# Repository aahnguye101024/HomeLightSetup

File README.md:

# HomeLightSetup
This project features 2 boards that work together to turn on strips of SK9822 wirelessly and either turn on them using my iphone with shortcuts through wifi or through the main board through a cap touch interface. The main board having an esp32 pico d4 with an antenna for WiFi access, a cap touch ic, and additions to support a lipo battery. The auxiliary board features an esp32 pico d4 with an antenna to communicate with the main board and a hefty 12V to 5V buck to run lights off of.

# Main Board

# Auxiliary Board

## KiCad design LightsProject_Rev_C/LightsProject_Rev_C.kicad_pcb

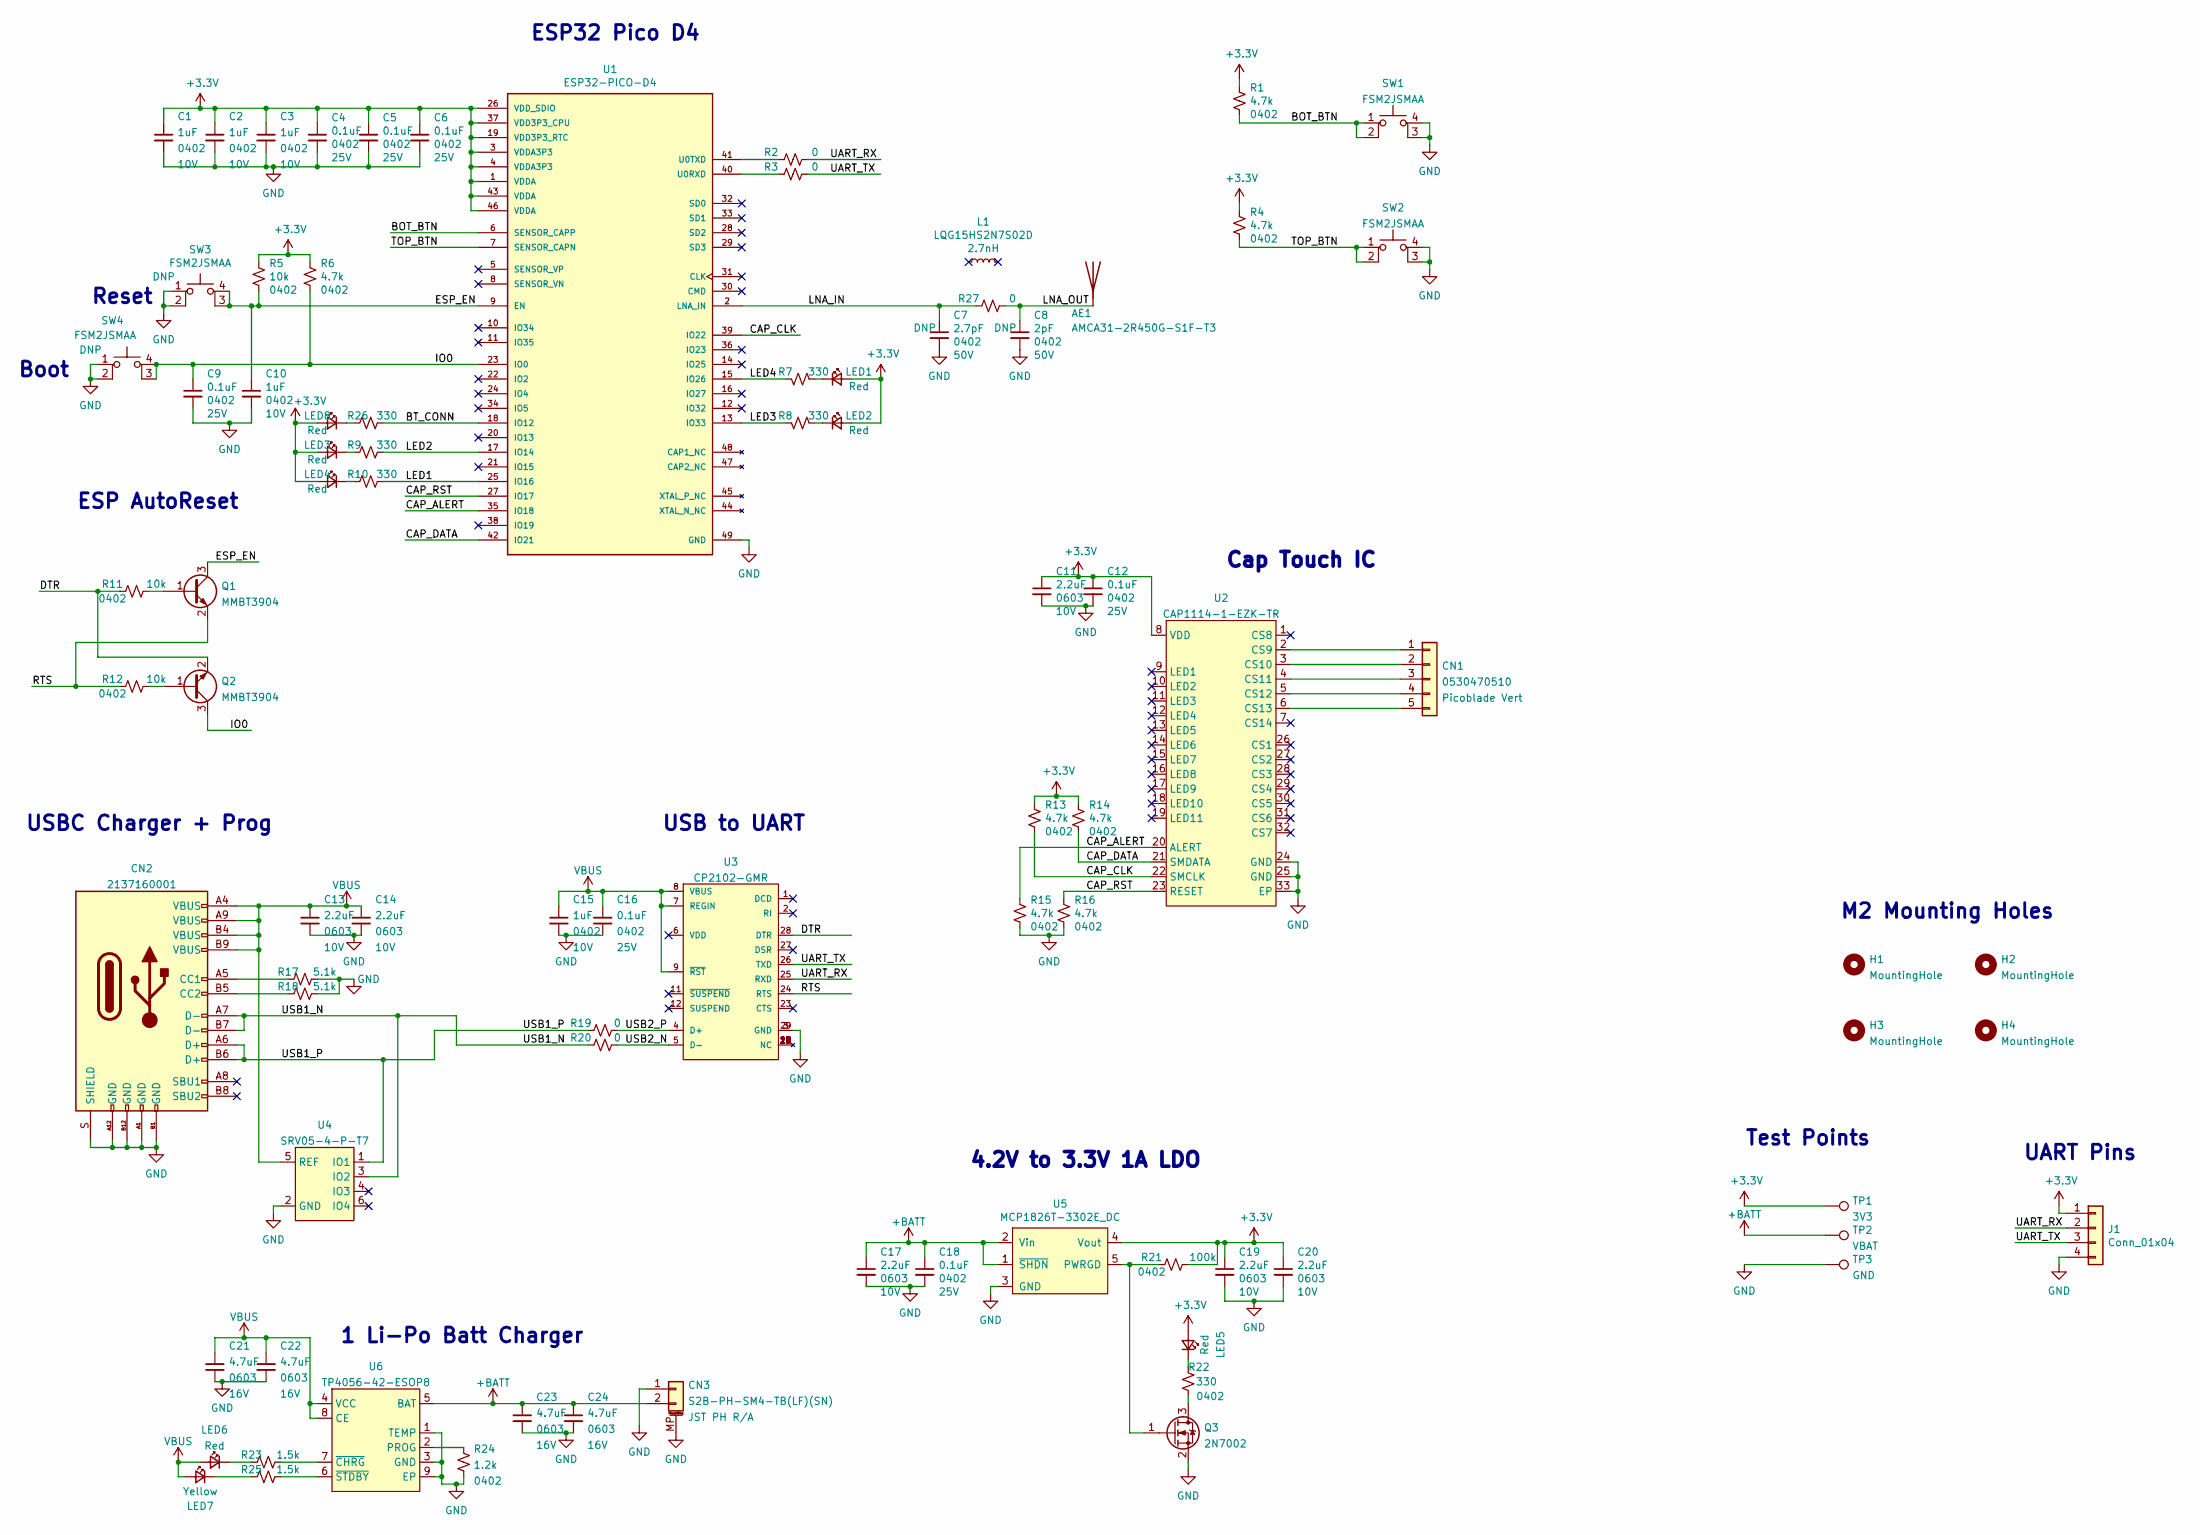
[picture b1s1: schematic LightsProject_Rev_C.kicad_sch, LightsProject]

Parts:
AE1: AMCA31-2R450G-S1F-T3; ANT_AMCA31-2R450G-S1F-T3; Part Number 535-14095-1-ND
C1, C2, C3, C10, C15: 1uF; C_0402_1005Metric; Voltage 10V; Part Number 1276-1076-1-ND
C4, C5, C6, C9, C12, C16, C18: 0.1uF; C_0402_1005Metric; Voltage 25V; Part Number 1276-1043-1-ND
C7: 2.7pF; C_0402_1005Metric; Voltage 50V; Part Number 311-1005-1-ND
C8: 2pF; C_0402_1005Metric; Voltage 50V; Part Number 311-1006-1-ND
C11, C13, C14, C17, C19, C20: 2.2uF; C_0603_1608Metric; Voltage 10V; Part Number 1276-1085-1-ND
C21, C22, C23, C24: 4.7uF; C_0603_1608Metric; Voltage 16V; Part Number 1276-1784-1-ND
CN1: 0530470510; Part Number WM1734-ND
CN2: 2137160001; Part Number 900-2137160001CT-ND
CN3: S2B-PH-SM4-TB(LF)(SN); JST_S2B-PH-SM4-TB(LF)(SN); Part Number 455-1749-1-ND
H1, H2, H3, H4: MountingHole; MountingHole_2.2mm_M2_ISO14580
J1: Conn_01x04; PinHeader_1x04_P2.54mm_Vertical
L1: LQG15HS2N7S02D; L_0402_1005Metric; Part Number 490-2615-1-ND
LED1, LED2, LED3, LED4, LED5, LED6, LED8: NCD0805R1; LED_0805_2012Metric; Part Number C84256
LED7: Y2C-CQ2R2L; LED_0603_1608Metric; Voltage 2.1V; Part Number C72038
Q1, Q2: MMBT3904; SOT-23; Part Number C20526
Q3: 2N7002; SOT-23; Part Number C8545; JLC Part Number C8545
R1, R4, R6, R13, R14, R15, R16: 4.7k; R_0402_1005Metric; Part Number RMCF0402FT4K70CT-ND
R2, R3, R19, R20, R27: 0; R_0402_1005Metric; Part Number RMCF0402ZT0R00CT-ND
R5, R11, R12: 10k; R_0402_1005Metric; Part Number RMCF0402FT10K0CT-ND
R7, R8, R9, R10, R22, R26: 330; R_0402_1005Metric; Part Number 311-330LRCT-ND
R17, R18: 5.1k; R_0402_1005Metric; Part Number 311-5.10KLRCT-ND
R21: 100k; R_0402_1005Metric; Part Number 2037-PFR05S-104-FNHCT-ND
R23, R25: 1.5k; R_0402_1005Metric; Part Number RMCF0402FT1K50CT-ND
R24: 1.2k; R_0402_1005Metric; Part Number YAG3447CT-ND
SW1, SW2, SW3, SW4: FSM2JSMAA; SW_2-1437565-8; Part Number 450-3355-ND
TP1: 3V3; CurrentTestPoint
TP2: VBAT; CurrentTestPoint
TP3: GND; CurrentTestPoint
U1: ESP32-PICO-D4; QFN-48-1EP_7x7mm_P0.5mm_EP5.3x5.3mm_ThermalVias; Part Number 1904-1029-1-ND
U2: CAP1114-1-EZK-TR; QFN-32-1EP_5x5mm_P0.5mm_EP3.1x3.1mm; Part Number Ologic
U3: CP2102-GMR; QFN28G_0.5-5X5MM; Part Number IC USB-TO-UART BRIDGE 28VQFN; JLC Part Number C6568
U4: SRV05-4-P-T7; SOT-23-6; Part Number C85364
U5: MCP1826T-3302E_DC; SOT-223-6_TabPin3; Part Number Ologic
U6: TP4056-42-ESOP8; HTSOP-8-1EP_3.9x4.9mm_P1.27mm_EP2.4x3.2mm; Part Number C16581

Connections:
+3V3: C1.1, C2.1, C3.1, C4.1, C5.1, C6.1, C11.1, C12.1, C19.1, C20.1, J1.1, LED1.2 (A), LED2.2 (A), LED3.2 (A), LED4.2 (A), LED5.2 (A), LED8.2 (A), R1.1, R4.1, R5.1, R6.1, R13.1, R14.1, R21.2, TP1.1, U1.1 (VDDA), U1.3 (VDDA3P3), U1.4 (VDDA3P3), U1.19 (VDD3P3_RTC), U1.26 (VDD_SDIO), U1.37 (VDD3P3_CPU), U1.43 (VDDA), U1.46 (VDDA), U2.8 (VDD), U5.4 (Vout)
+BATT: C17.1, C18.1, C23.1, C24.1, CN3.2, TP2.1, U5.1 (~SHDN), U5.2 (Vin), U6.5 (BAT)
/BOT_BTN: R1.2, SW1.1, SW1.2, U1.6 (SENSOR_CAPP)
/BT_CONN: R26.1, U1.18 (IO12)
/CAP_ALERT: R15.1, U1.35 (IO18), U2.20 (ALERT)
/CAP_CLK: R13.2, U1.39 (IO22), U2.22 (SMCLK)
/CAP_DATA: R14.2, U1.42 (IO21), U2.21 (SMDATA)
/CAP_RST: R16.1, U1.27 (IO17), U2.23 (RESET)
/DTR: Q2.2 (E), R11.2, U3.28 (DTR)
/ESP_EN: C10.1, Q1.3 (C), R5.2, SW3.3 (K), SW3.4 (A), U1.9 (EN)
/IO0: C9.1, Q2.3 (C), R6.2, SW4.3 (K), SW4.4 (A), U1.23 (IO0)
/LED1: R10.1, U1.25 (IO16)
/LED2: R9.1, U1.17 (IO14)
/LED3: R8.1, U1.13 (IO33)
/LED4: R7.1, U1.15 (IO26)
/LNA_IN: C7.1, R27.2, U1.2 (LNA_IN)
/LNA_OUT: AE1.1 (A), C8.1, R27.1
/RTS: Q1.2 (E), R12.2, U3.24 (RTS)
/TOP_BTN: R4.2, SW2.1, SW2.2, U1.7 (SENSOR_CAPN)
/UART_RX: J1.2, R2.1, U3.25 (RXD)
/UART_TX: J1.3, R3.1, U3.26 (TXD)
/USB1_N: CN2.A7 (D-), CN2.B7 (D-), R20.1, U4.3 (IO2)
/USB1_P: CN2.A6 (D+), CN2.B6 (D+), R19.1, U4.1 (IO1)
/USB2_N: R20.2, U3.5 (D-)
/USB2_P: R19.2, U3.4 (D+)
GND: C1.2, C2.2, C3.2, C4.2, C5.2, C6.2, C7.2, C8.2, C9.2, C10.2, C11.2, C12.2, C13.2, C14.2, C15.2, C16.2, C17.2, C18.2, C19.2, C20.2, C21.2, C22.2, C23.2, C24.2, CN2.A1 (GND), CN2.A12 (GND), CN2.B1 (GND), CN2.B12 (GND), CN2.S (SHIELD), CN3.1, CN3.MP (MountPin), J1.4, Q3.2 (S), R15.2, R16.2, R17.2, R18.2, R24.2, SW1.3 (K), SW1.4 (A), SW2.3 (K), SW2.4 (A), SW3.1, SW3.2, SW4.1, SW4.2, TP3.1, U1.49 (GND), U2.24 (GND), U2.25 (GND), U2.33 (EP), U3.3 (GND), U3.29 (GND), U4.2 (GND), U5.3 (GND), U6.1 (TEMP), U6.3 (GND), U6.9 (EP)
unnamed: CN1.1, U2.2 (CS9)
unnamed: CN1.2, U2.3 (CS10)
unnamed: CN1.3, U2.4 (CS11)
unnamed: CN1.4, U2.5 (CS12)
unnamed: CN1.5, U2.6 (CS13)
unnamed: CN2.A5 (CC1), R17.1
unnamed: CN2.B5 (CC2), R18.1
unnamed: LED1.1 (K), R7.2
unnamed: LED2.1 (K), R8.2
unnamed: LED3.1 (K), R9.2
unnamed: LED4.1 (K), R10.2
unnamed: LED5.1 (K), R22.2
unnamed: LED6.1 (K), R23.1
unnamed: LED7.1 (K), R25.1
unnamed: LED8.1 (K), R26.2
unnamed: Q1.1 (B), R11.1
unnamed: Q2.1 (B), R12.1
unnamed: Q3.1 (G), R21.1, U5.5 (PWRGD)
unnamed: Q3.3 (D), R22.1
unnamed: R2.2, U1.41 (U0TXD)
unnamed: R3.2, U1.40 (U0RXD)
unnamed: R23.2, U6.7 (~CHRG)
unnamed: R24.1, U6.2 (PROG)
unnamed: R25.2, U6.6 (~STDBY)
VBUS: C13.1, C14.1, C15.1, C16.1, C21.1, C22.1, CN2.A4 (VBUS), CN2.A9 (VBUS), CN2.B4 (VBUS), CN2.B9 (VBUS), LED6.2 (A), LED7.2 (A), U3.7 (REGIN), U3.8 (VBUS), U3.9 (~RST), U4.5 (REF), U6.4 (VCC), U6.8 (CE)

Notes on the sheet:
1 Li-Po Batt Charger
ESP32 Pico D4
UART Pins
USBC Charger + Prog
Test Points
M2 Mounting Holes
ESP AutoReset
Reset
USB to UART
Cap Touch IC
Boot
4.2V to 3.3V 1A LDO

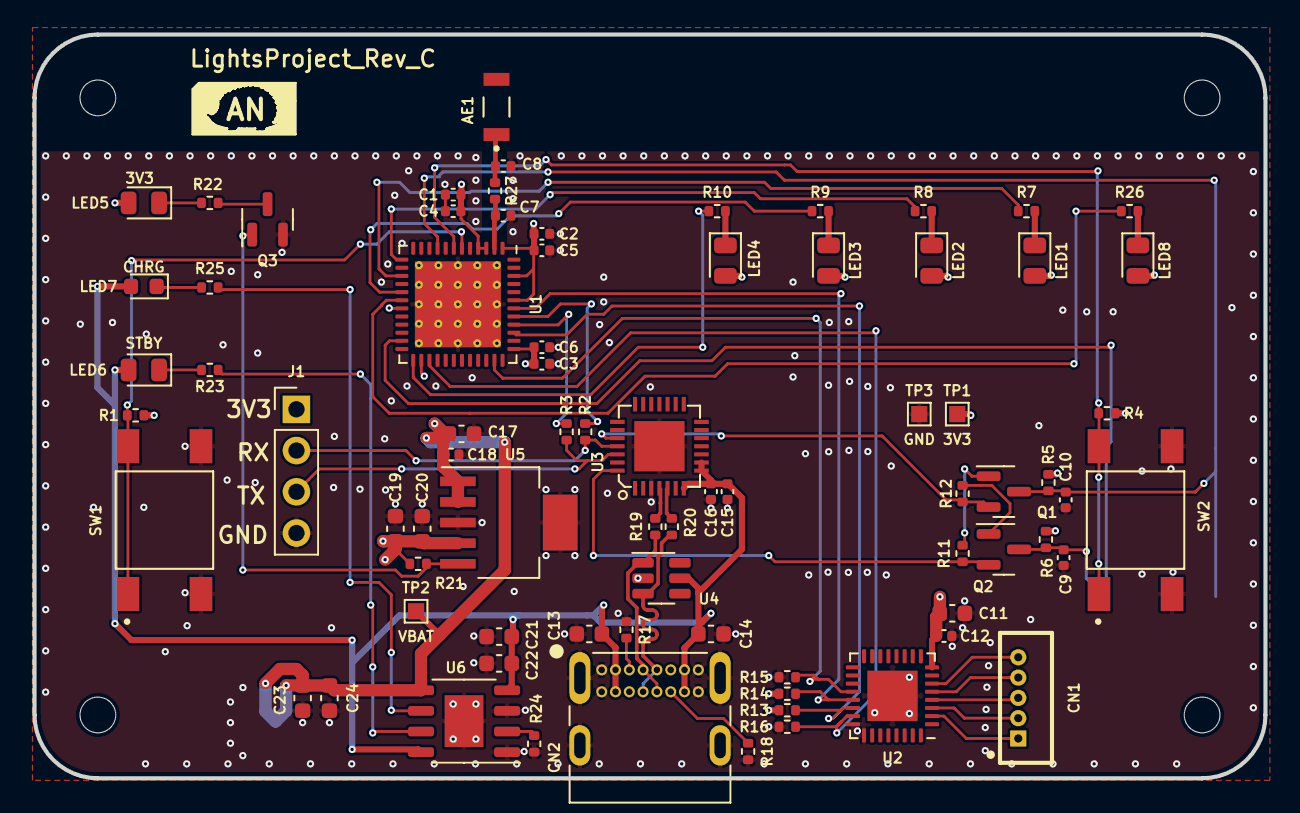
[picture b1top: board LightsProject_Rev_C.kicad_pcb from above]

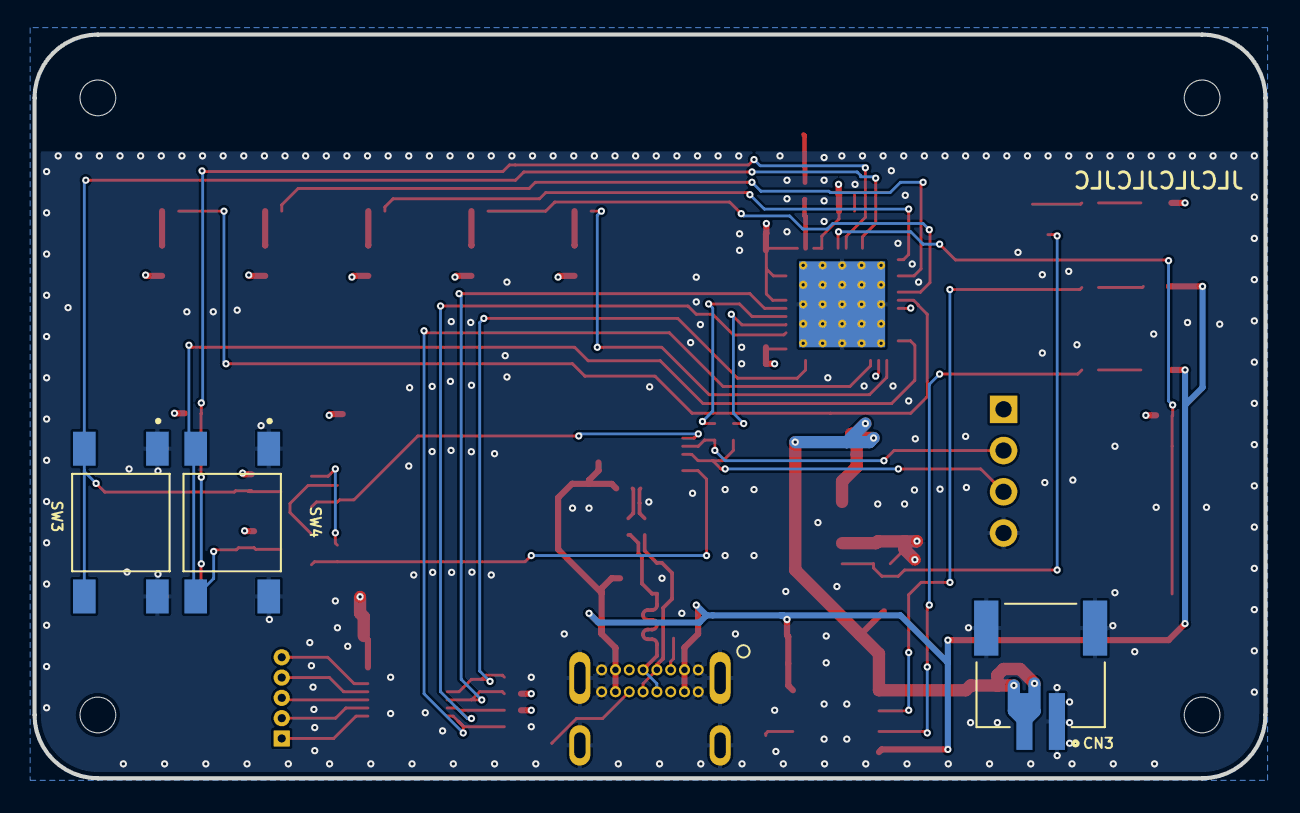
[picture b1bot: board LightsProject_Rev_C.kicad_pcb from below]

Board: 4 copper layers, 75.8 x 45.8 mm, 84 parts (3 on the bottom side), 51 nets.

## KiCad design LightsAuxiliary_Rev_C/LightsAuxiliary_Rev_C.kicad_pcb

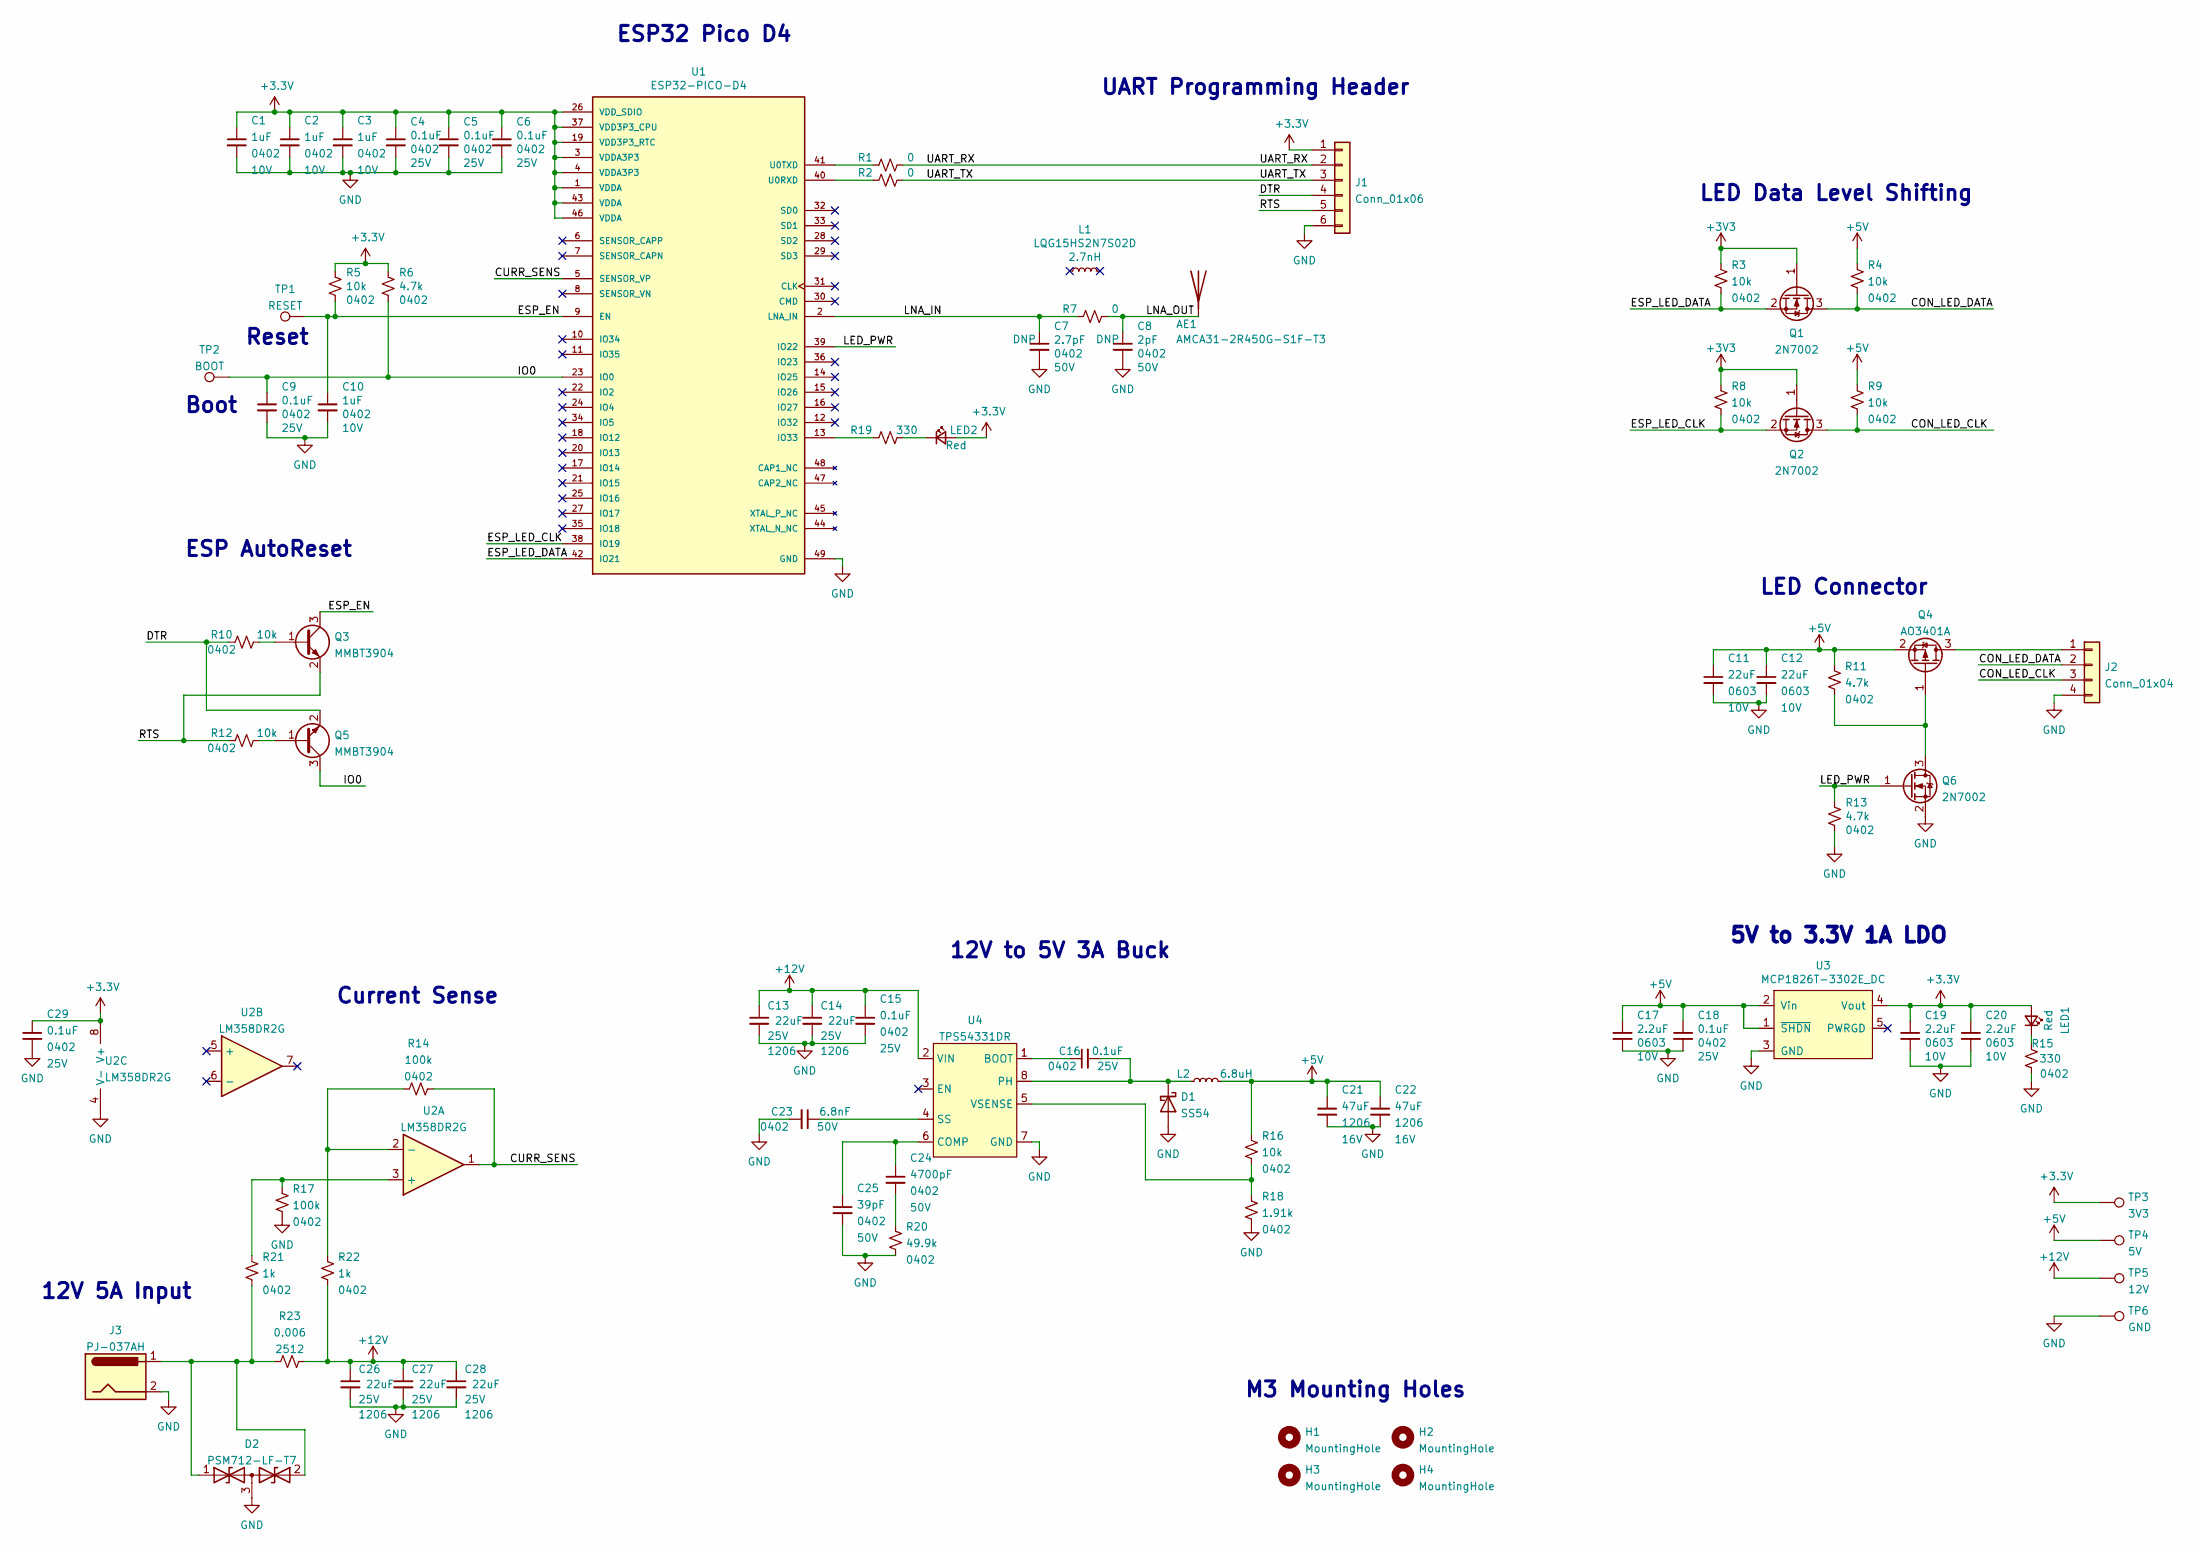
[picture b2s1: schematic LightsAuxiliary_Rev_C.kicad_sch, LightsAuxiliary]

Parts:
AE1: AMCA31-2R450G-S1F-T3; ANT_AMCA31-2R450G-S1F-T3; Part Number 535-14095-1-ND
C1, C2, C3, C10: 1uF; C_0402_1005Metric; Voltage 10V; Part Number 1276-1076-1-ND
C4, C5, C6, C9, C15, C16, C18, C29: 0.1uF; C_0402_1005Metric; Voltage 25V; Part Number 1276-1043-1-ND
C7: 2.7pF; C_0402_1005Metric; Voltage 50V; Part Number 311-1005-1-ND
C8: 2pF; C_0402_1005Metric; Voltage 50V; Part Number 311-1006-1-ND
C11, C12: 22uF; C_0603_1608Metric; Voltage 10V; Part Number 1276-1274-1-ND
C13, C14, C26, C27, C28: 22uF_1206; C_1206_3216Metric; Voltage 25V; Part Number 1276-3047-1-ND
C17, C19, C20: 2.2uF; C_0603_1608Metric; Voltage 10V; Part Number 1276-1085-1-ND
C21, C22: 47uF; C_1206_3216Metric; Voltage 16V; Part Number 587-5425-1-ND
C23: 6.8nF; C_0402_1005Metric; Voltage 50V; Part Number 399-C0402C682K5RECAUTOCT-ND
C24: 4700pF; C_0402_1005Metric; Voltage 50V; Part Number 311-1418-1-ND
C25: 39pF; C_0402_1005Metric; Voltage 50V; Part Number 490-5871-1-ND
D1: SS54; D_SMA; Part Number C22452
D2: PSM712-LF-T7; SOT-23; Part Number C32677
H1, H2, H3, H4: MountingHole; MountingHole_3.2mm_M3_ISO7380
J1: Conn_01x06; PinHeader_1x06_P2.54mm_Vertical
J2: Conn_01x04; PinHeader_1x04_P2.54mm_Horizontal
J3: PJ-037AH; CUI_PJ-037AH; Part Number PJ-037AH
L1: LQG15HS2N7S02D; L_0402_1005Metric; Part Number 490-2615-1-ND
L2: SLO0530H6R8MTT; Part Number C325965
LED1, LED2: NCD0805R1; LED_0805_2012Metric; Part Number C84256
Q1, Q2, Q6: 2N7002; SOT-23; Part Number C8545; JLC Part Number C8545
Q3, Q5: MMBT3904; SOT-23; Part Number C20526
Q4: AO3401A; SOT-23W; Part Number C15127; JLC Part Number C15127
R1, R2, R7: 0; R_0402_1005Metric; Part Number RMCF0402ZT0R00CT-ND
R3, R4, R5, R8, R9, R10, R12, R16: 10k; R_0402_1005Metric; Part Number RMCF0402FT10K0CT-ND
R6, R11, R13: 4.7k; R_0402_1005Metric; Part Number RMCF0402FT4K70CT-ND
R14, R17: 100k; R_0402_1005Metric; Part Number 2037-PFR05S-104-FNHCT-ND
R15, R19: 330; R_0402_1005Metric; Part Number 311-330LRCT-ND
R18: 1.91k; R_0402_1005Metric; Part Number RMCF0402FT1K91CT-ND
R20: 49.9k; R_0402_1005Metric; Part Number RMCF0402FT49K9CT-ND
R21, R22: 1k; R_0402_1005Metric; Part Number RMCF0402FT1K00CT-ND
R23: 0.006; R_2512_6332Metric; Part Number YAG2146CT-ND
TP1: RESET; CurrentTestPoint
TP2: BOOT; CurrentTestPoint
TP3: 3V3; CurrentTestPoint
TP4: 5V; CurrentTestPoint
TP5: 12V; CurrentTestPoint
TP6: GND; CurrentTestPoint
U1: ESP32-PICO-D4; QFN-48-1EP_7x7mm_P0.5mm_EP5.3x5.3mm_ThermalVias; Part Number 1904-1029-1-ND
U2: LM358DR2G; SOIC-8_3.9x4.9mm_P1.27mm; Part Number C7950
U3: MCP1826T-3302E_DC; SOT-223-6_TabPin3; Part Number Ologic
U4: TPS54331DR; SOIC-8_3.9x4.9mm_P1.27mm; Part Number 296-26991-1-ND

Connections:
+5V: C11.1, C12.1, C17.1, C18.1, C21.1, C22.1, L2.2, Q4.2 (S), R4.1, R9.1, R11.1, R16.1, TP4.1, U3.1 (~SHDN), U3.2 (Vin)
+12V: C13.1, C14.1, C15.1, C26.1, C27.1, C28.1, R22.2, R23.2, TP5.1, U4.2 (VIN)
/CON_LED_CLK: J2.3, Q2.3 (D), R9.2
/CON_LED_DATA: J2.2, Q1.3 (D), R4.2
/CURR_SENS: R14.2, U1.5 (SENSOR_VP), U2.1
/DTR: J1.4, Q5.2 (E), R10.2
/ESP_EN: C10.1, Q3.3 (C), R5.2, TP1.1, U1.9 (EN)
/ESP_LED_CLK: Q2.2 (S), R8.2, U1.38 (IO19)
/ESP_LED_DATA: Q1.2 (S), R3.2, U1.42 (IO21)
/IO0: C9.1, Q5.3 (C), R6.2, TP2.1, U1.23 (IO0)
/LED_PWR: Q6.1 (G), R13.1, U1.39 (IO22)
/LNA_IN: C7.1, R7.2, U1.2 (LNA_IN)
/LNA_OUT: AE1.1 (A), C8.1, R7.1
/RTS: J1.5, Q3.2 (E), R12.2
/UART_RX: J1.2, R1.1
/UART_TX: J1.3, R2.1
GND: C1.2, C2.2, C3.2, C4.2, C5.2, C6.2, C7.2, C8.2, C9.2, C10.2, C11.2, C12.2, C13.2, C14.2, C15.2, C17.2, C18.2, C19.2, C20.2, C21.2, C22.2, C23.2, C25.2, C26.2, C27.2, C28.2, C29.2, D1.2 (A), D2.3 (common), J1.6, J2.4, J3.2, Q6.2 (S), R13.2, R15.1, R17.2, R18.2, R20.2, TP6.1, U1.49 (GND), U2.4 (V-), U3.3 (GND), U4.7 (GND)
unnamed: C16.1, U4.1 (BOOT)
unnamed: C16.2, D1.1 (K), L2.1, U4.8 (PH)
unnamed: C23.1, U4.4 (SS)
unnamed: C24.1, C25.1, U4.6 (COMP)
unnamed: C24.2, R20.1
unnamed: D2.1 (A1), D2.2 (A2), J3.1, R21.2, R23.1
unnamed: J2.1, Q4.3 (D)
unnamed: LED1.1 (K), R15.2
unnamed: LED2.1 (K), R19.2
unnamed: Q3.1 (B), R10.1
unnamed: Q4.1 (G), Q6.3 (D), R11.2
unnamed: Q5.1 (B), R12.1
unnamed: R1.2, U1.41 (U0TXD)
unnamed: R2.2, U1.40 (U0RXD)
unnamed: R14.1, R22.1, U2.2 (-)
unnamed: R16.2, R18.1, U4.5 (VSENSE)
unnamed: R17.1, R21.1, U2.3 (+)
unnamed: R19.1, U1.13 (IO33)

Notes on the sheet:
Reset
5V to 3.3V 1A LDO
LED Connector
Boot
12V to 5V 3A Buck
ESP AutoReset
LED Data Level Shifting
M3 Mounting Holes
UART Programming Header
Current Sense
12V 5A Input
ESP32 Pico D4

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
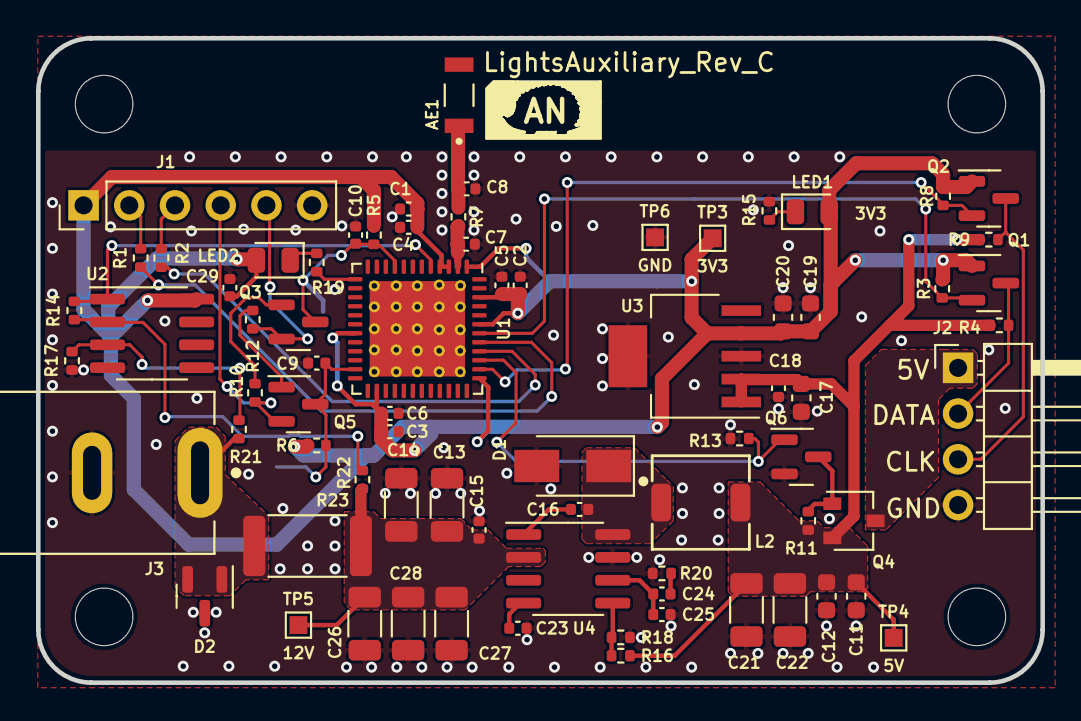
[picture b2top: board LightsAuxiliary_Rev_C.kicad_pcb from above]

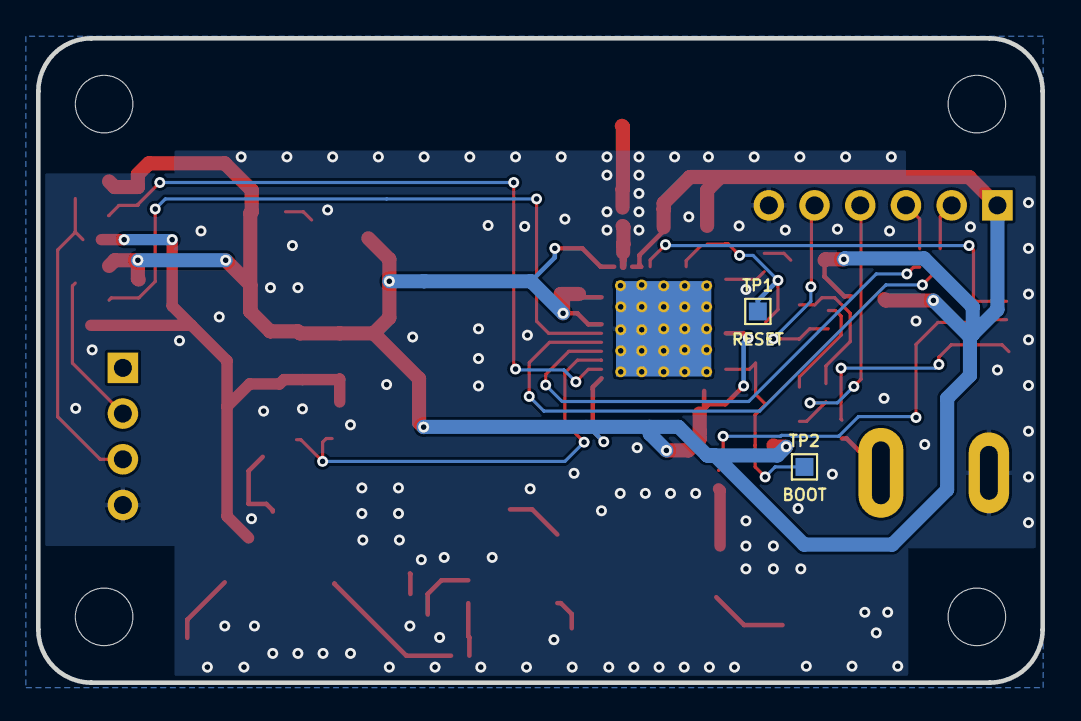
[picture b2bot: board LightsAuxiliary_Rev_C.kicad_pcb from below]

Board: 2 copper layers, 55.8 x 35.8 mm, 81 parts (2 on the bottom side), 36 nets.

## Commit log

2024-01-31 initial Commid
2024-01-31 Updated read me
